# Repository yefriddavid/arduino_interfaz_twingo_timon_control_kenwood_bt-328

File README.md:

# Arduino Interfaz Twingo Timon Control Kenwood BT-328

### References:
- https://www.kenwood.com/pa/car/head_units/kmm-bt328/
- https://articulo.mercadolibre.com.co/MCO-555947676-control-de-audio-ve-interfaz-para-twingo-clio-y-symbol-_JM#backend=item_decorator&backend_type=function&client=bookmarks-polycard
- https://github.com/bigevtaylor/arduino-swc
- https://www.instructables.com/Custom-Arduino-to-Keep-CAN-Steering-Wheel-Buttons-/
- https://www.youtube.com/watch?v=epe_4fnpTjk&ab_channel=JustinNelson%27sProjects
- https://github.com/tsprlng/toyota-kenwood-adaptor ## works
- http://drclone.blogspot.com/2015/01/controlar-autorradio-sony-con-los.html
- https://www.youtube.com/watch?v=6VO589mRQkM&ab_channel=TravisColesen
- https://www.youtube.com/watch?v=RdR43ACfeu8&t=257s&ab_channel=MentalidadDeIngenier%C3%ADa
- https://www.youtube.com/watch?v=d-j0onzzuNQ&t=305s&ab_channel=TheEngineeringMindset
- https://lastminuteengineers.com/esp8266-pinout-reference/
- https://randomnerdtutorials.com/esp8266-pinout-reference-gpios/
- https://www.kenwood.com/asia/car/Steering-remote/
- https://www.youtube.com/watch?v=fk73SCOE8qU&ab_channel=BartKuijper
- https://pastebin.com/fXbScxV4 // code with jvc and twingo
- https://init6.pomorze.pl/projects/kenwood_ford/

### Pinout
- https://lastminuteengineers.com/esp8266-pinout-reference/
- https://lededitpro.com/esp8266-pinout-guide-gpios/

### 

- https://www.youtube.com/watch?v=vRJ6ywV8bLI&ab_channel=Electr%C3%B3nicaAWV
- https://randomnerdtutorials.com/esp8266-pinout-reference-gpios/

### Commands
```
$ make upload
$ make compile
$ make just-compile
```

| Pin		|     Arnes Color 	|   ESP8266 Pin	| Card	Control Color	|
|---------------|-----------------------|---------------|-----------------------|
| 4		| 	Green		| 	D2 	|	Green 		|
| 2	 	| 	White 		|	D4 	|	Brown 		|
| 15 	 	| 	Yellow		|	D8 	|	Yellow 		|
| 12 	 	| 	Blue		|	D6 	|	Light Blue 	|
| 13 		| 	White/Brown 	|	D7 	|	Black		|		
| 14 	 	| 	White/Orange 	|	D5 	|	Red 		|

| 	   Wire     	|     Brown 	|   	Blak	| 	Red	|
|-----------------------|---------------|---------------|---------------|
| 	Green		|    RULETA	| SKIP_FORWARD  |    SOURCE     |
| 	Yellow		|    RULETA	| SKIP_BACKWARD  |   VOL DOWN    |
| 	Blue		|    RULETA 	|    MUTE       |    VOL UP     |

```

D4 -> 2
D8 -> 15
D2 -> 4
D6 -> 12
D5 -> 14
D1 -> 5 -> Stereo Output -> kenwood

```

```
Red Wire -> Ignition stereo car
Black Wire -> Negative Stereo Wire harness
Yellow Wire -> light/blue Wire Stero Harness

```

### Command
<!---->

### Twingo Access

## New features
- beep: to know if the device started, from driver's seat

## Green Output (OK) only works for leds or something like

## Kendood BT-328

## Twingo Timon Control

## Case

## Wire

## NEC

## PCB

## PINOUT PWM

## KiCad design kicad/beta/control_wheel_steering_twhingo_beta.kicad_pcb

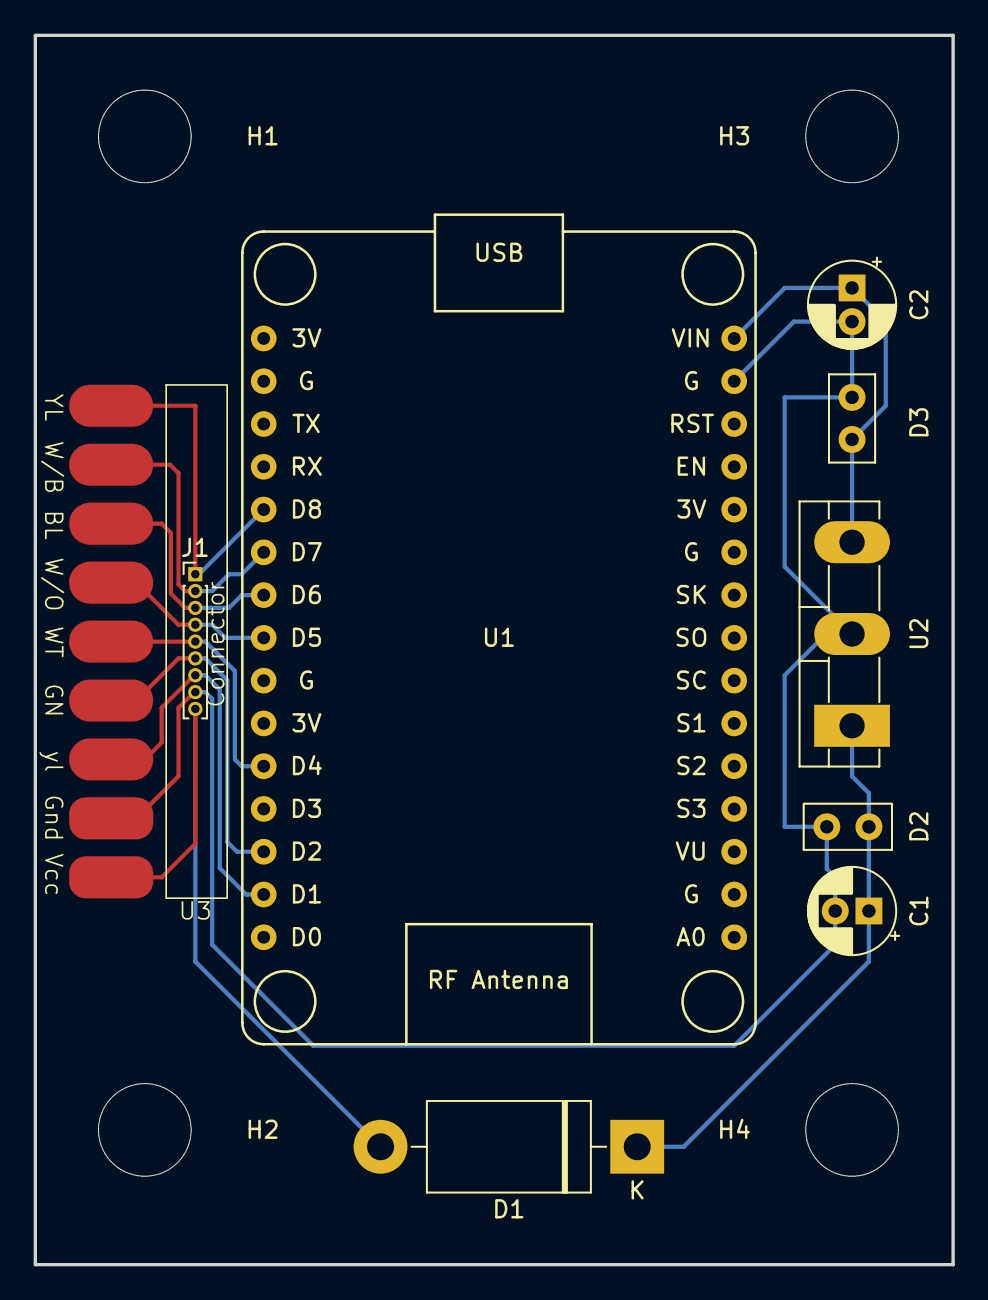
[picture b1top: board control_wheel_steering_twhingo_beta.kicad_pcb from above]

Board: 2 copper layers, 54.5 x 73.0 mm, 13 parts (0 on the bottom side), 9 nets.

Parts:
C1: Cap2; CP_Radial_D5.0mm_P2.00mm
C2: C_Polarized; CP_Radial_D5.0mm_P2.00mm
D1: 1N5408; D_DO-201AD_P15.24mm_Horizontal
D2, D3: cap1; C_Disc_D5.0mm_W2.5mm_P2.50mm
H1, H2, H3, H4: MountingHole; MountingHole_5.5mm
J1: Conn_01x09_Socket; PinHeader_1x09_P1.00mm_Vertical
U1: NodeMCU_1.0_(ESP-12E); NodeMCU1.0(12-E)
U2: L7805; TO-3P-3_Vertical
U3: Twingo_Timon_Control_Connector

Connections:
D2Green: J1.6, U3.6 (D2)
D4-White: J1.5, U3.5 (D4)
D5-White/Orange: J1.4, U3.4 (D5)
D6-Blue: J1.3, U3.3 (D6)
D7-WhiteBrown: J1.2, U3.2 (D7)
D8-Yellow: J1.1, U3.1 (D8)
Gnd: J1.8, U3.8 (GND)
StereoOut: J1.7, U3.7 (StrOut)
VinCar: J1.9, U3.9 (Vin)

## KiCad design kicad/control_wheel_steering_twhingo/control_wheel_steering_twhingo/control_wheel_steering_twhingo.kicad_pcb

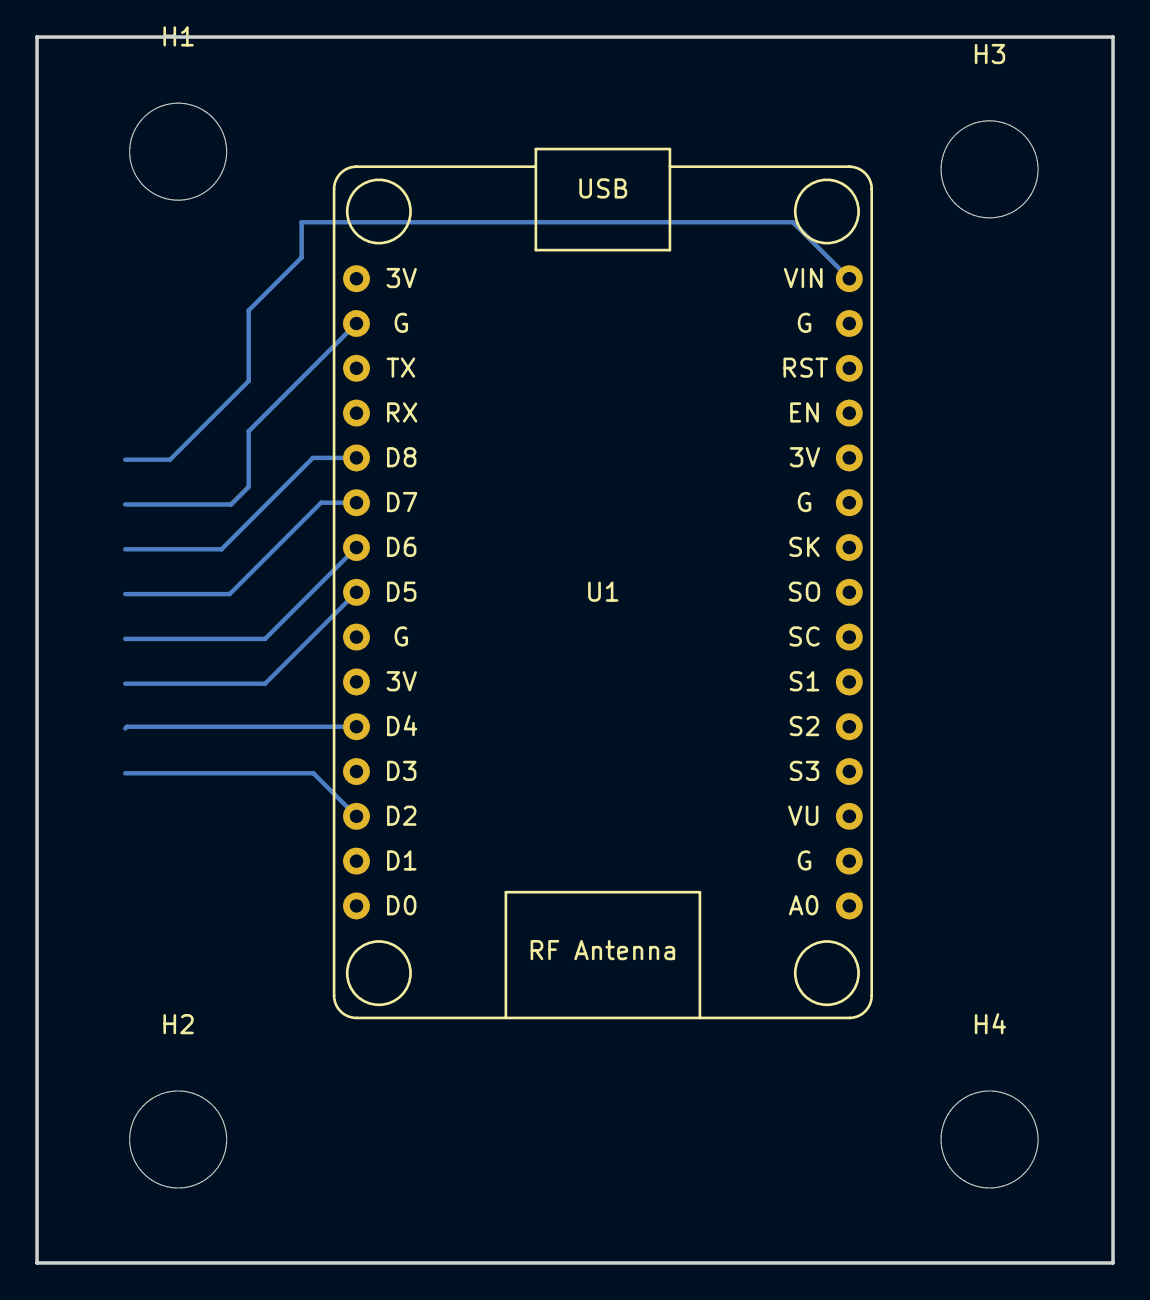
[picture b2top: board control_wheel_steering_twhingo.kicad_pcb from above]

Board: 2 copper layers, 61.0 x 69.5 mm, 6 parts (1 on the bottom side), 8 nets.

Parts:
H1, H2, H3, H4: MountingHole; MountingHole_5.5mm
J1: Conn_01x09_Socket; Harting_har-flexicon_14110813010xxx_1x08-MP_P2.54mm_Horizon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
U1: NodeMCU_1.0_(ESP-12E); NodeMCU1.0(12-E)

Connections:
D2-White: J1.8, U1.28 (D2(GPIO4))
D4-Brawn: J1.7, U1.26 (D4(GPIO2))
D5-Red: J1.6, U1.23 (D5(GPIO14))
D6-Blue: J1.5, U1.22 (D6(GPIO12))
D7-White/Orange: J1.4, U1.21 (D7(GPIO13))
D8-Yellow: J1.3, U1.20 (D8(GPIO15))
GND: J1.2, U1.17 (GND)
Vin: J1.1, U1.15 (VIN)

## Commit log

2022-10-19 base code
2022-10-25 docs
2022-10-27 first version with bug with vol up run sometimes source too
2022-10-27 polish files
2022-10-27 polish code
2022-11-01 add image
2022-11-01 added makefile
2022-11-01 installed version
2022-11-01 docs: wires
2022-11-02 docs: pins tables
2022-11-02 docs: pins table
2023-08-01 implement taskfile and docs
2023-08-01 implement kicad files
2023-08-01 implement taskfile
2023-08-01 openscad added
2023-08-01 polish directory
2023-08-02 openscad added beta
2023-08-02 docs image
2023-08-02 images of legacy
2023-08-03 3d box avances
2023-08-03 improve 3d case
2023-08-04 improve 3d box
